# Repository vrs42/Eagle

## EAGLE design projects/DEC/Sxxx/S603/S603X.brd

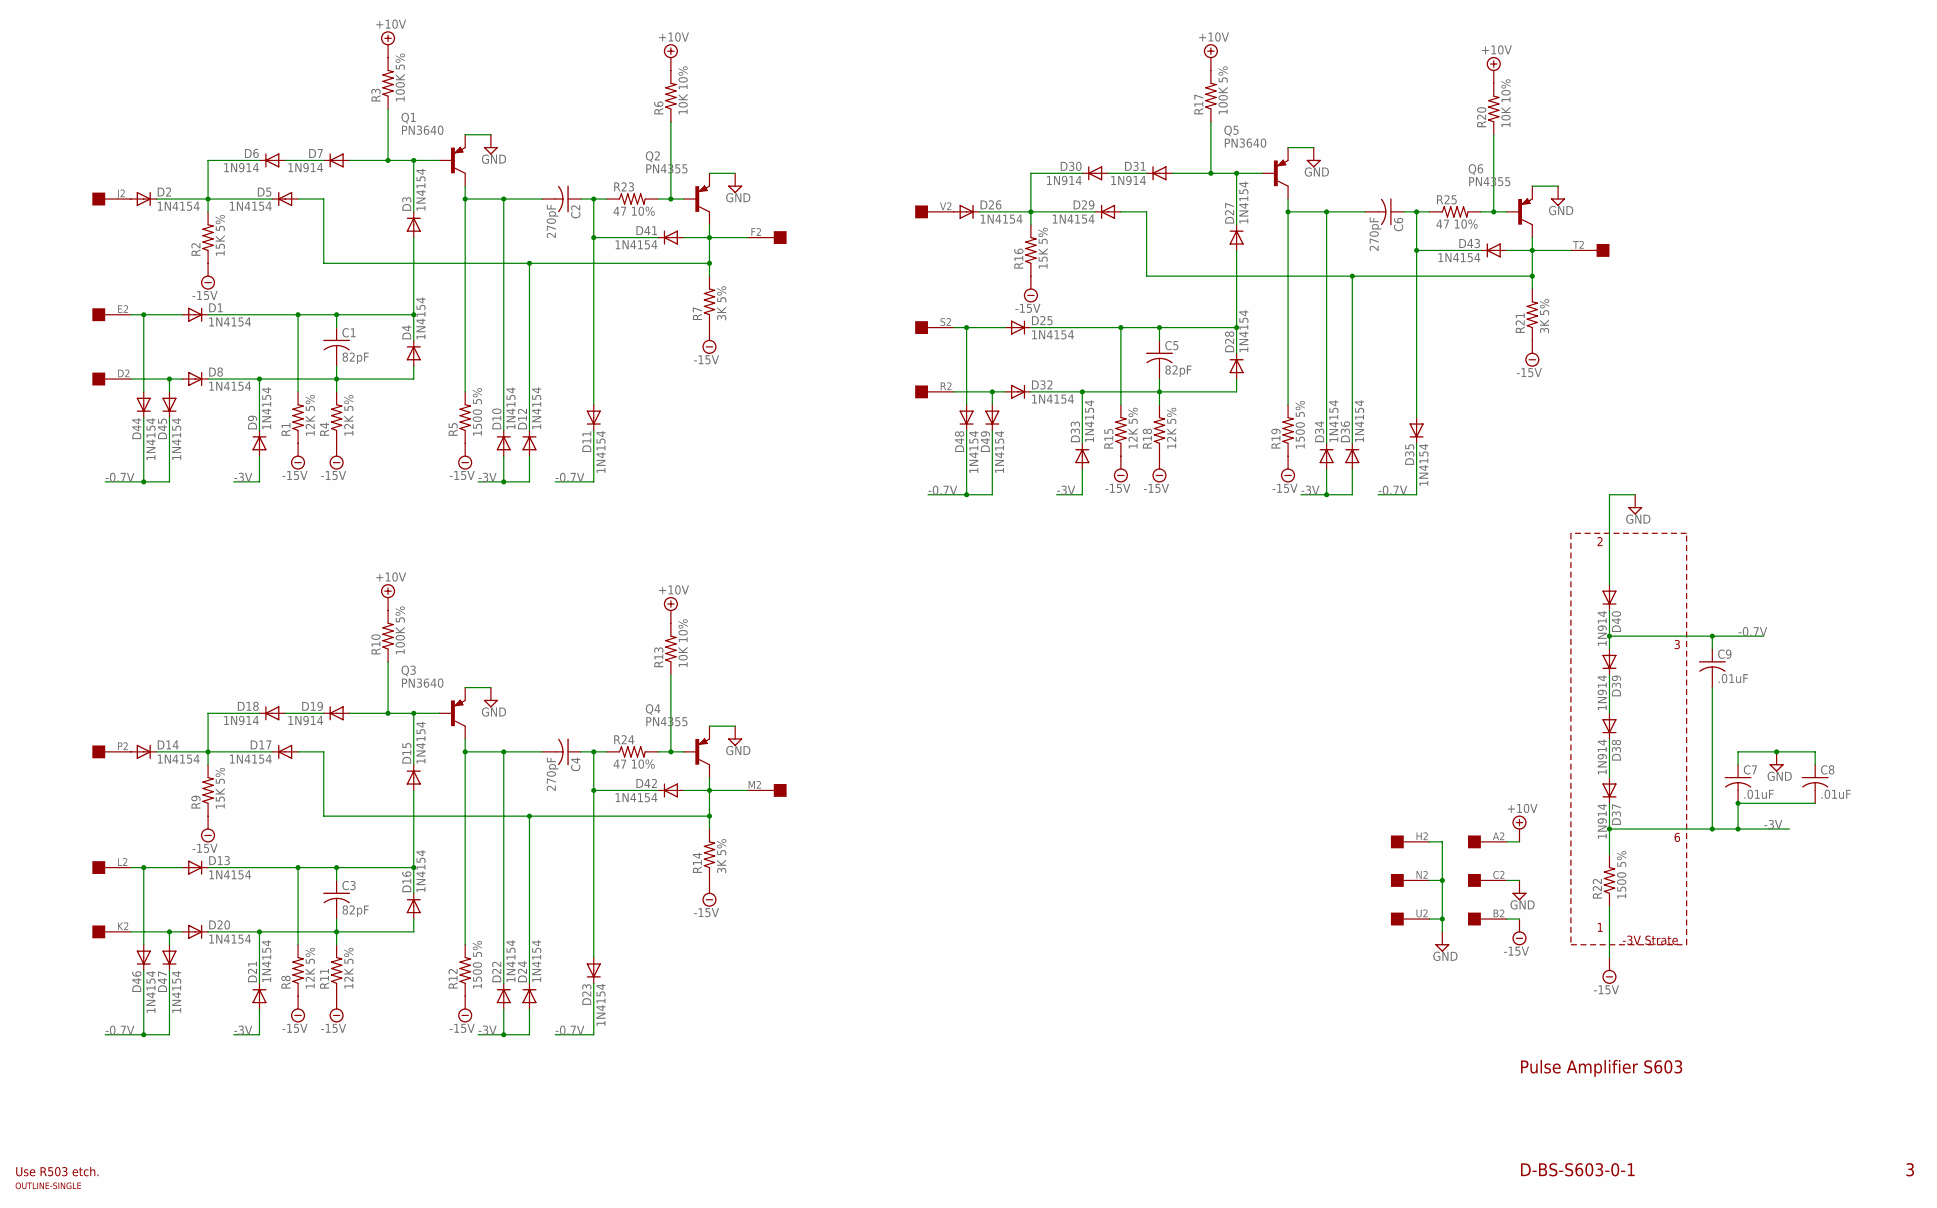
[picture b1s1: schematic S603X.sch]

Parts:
C1, C3, C5: 82pF; C050-025X075
C2, C4, C6: 270pF; C050-025X075
C7, C8, C9: .01uF; C050-025X075
D1, D2, D3, D4, D5, D8, D9, D10, D11, D12, D13, D14, D15, D16, D17, D20, D21, D22, D23, D24, D25, D26, D27, D28, D29, D32, D33, D34, D35, D36, D41, D42, D43, D44, D45, D46, D47, D48, D49: 1N4154; DO35-10
D6, D7, D18, D19, D30, D31, D37, D38, D39, D40: 1N914; DO35-10
Q1, Q3, Q5: PN3640; TO39
Q2, Q4, Q6: PN4355; TO39
R1, R4, R8, R11, R15, R18: 12K 5%; 0207/10
R2, R9, R16: 15K 5%; 0207/10
R3, R10, R17: 100K 5%; 0207/10
R5, R12, R19, R22: 1500 5%; 0207/10
R6, R13, R20: 10K 10%; 0207/10
R7, R14, R21: 3K 5%; 0207/10
R23, R24, R25: 47 10%; 0207/10
U$1: OUTLINE-SINGLE; SINGLE
U$2: EDGE-1; EDGE-CON1

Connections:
+10V: R3.2, R6.2, R10.2, R13.2, R17.2, R20.2, U$2.A2
-0.7V: C9.1, D11.C, D23.C, D35.C, D39.A, D40.C, D44.C, D45.C, D46.C, D47.C, D48.C, D49.C
-3V: C7.2, C8.2, C9.2, D9.A, D10.A, D12.A, D21.A, D22.A, D24.A, D33.A, D34.A, D36.A, D37.C, R22.2
-15V: R1.1, R2.1, R4.1, R5.1, R7.1, R8.1, R9.1, R11.1, R12.1, R14.1, R15.1, R16.1, R18.1, R19.1, R21.1, R22.1, U$2.B2
GND: C7.1, C8.1, D40.A, Q1.1 (E), Q2.1 (E), Q3.1 (E), Q4.1 (E), Q5.1 (E), Q6.1 (E), U$2.C2, U$2.H2, U$2.N2, U$2.U2
unnamed: D2.A, U$2.J2
unnamed: D2.C, D5.C, D6.C, R2.2
unnamed: D1.A, D44.A, U$2.E2
unnamed: D8.A, D45.A, U$2.D2
unnamed: C1.1, D1.C, D3.A, D4.C, R1.2
unnamed: C1.2, D4.A, D8.C, D9.C, R4.2
unnamed: D6.A, D7.C
unnamed: D38.A, D39.C
unnamed: D37.A, D38.C
unnamed: D3.C, D7.A, Q1.2 (B), R3.1
unnamed: C2.2, D10.C, Q1.3 (C), R5.2
unnamed: C2.1, D11.A, D41.C, R23.1
unnamed: Q2.2 (B), R6.1, R23.2
unnamed: D5.A, D12.C, D41.A, Q2.3 (C), R7.2, U$2.F2
unnamed: D13.A, D46.A, U$2.L2
unnamed: D20.A, D47.A, U$2.K2
unnamed: C3.1, D13.C, D15.A, D16.C, R8.2
unnamed: C3.2, D16.A, D20.C, D21.C, R11.2
unnamed: D25.A, D48.A, U$2.S2
unnamed: D32.A, D49.A, U$2.R2
unnamed: C5.1, D25.C, D27.A, D28.C, R15.2
unnamed: C5.2, D28.A, D32.C, D33.C, R18.2
unnamed: D26.A, U$2.V2
unnamed: D26.C, D29.C, D30.C, R16.2
unnamed: D30.A, D31.C
unnamed: D27.C, D31.A, Q5.2 (B), R17.1
unnamed: C6.2, D34.C, Q5.3 (C), R19.2
unnamed: C6.1, D35.A, D43.C, R25.1
unnamed: Q6.2 (B), R20.1, R25.2
unnamed: D29.A, D36.C, D43.A, Q6.3 (C), R21.2, U$2.T2
unnamed: D14.A, U$2.P2
unnamed: D14.C, D17.C, D18.C, R9.2
unnamed: D18.A, D19.C
unnamed: D15.C, D19.A, Q3.2 (B), R10.1
unnamed: C4.2, D22.C, Q3.3 (C), R12.2
unnamed: C4.1, D23.A, D42.C, R24.1
unnamed: Q4.2 (B), R13.1, R24.2
unnamed: D17.A, D24.C, D42.A, Q4.3 (C), R14.2, U$2.M2

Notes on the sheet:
Pulse Amplifier S603
D-BS-S603-0-1
-3V Strate
Use R503 etch.

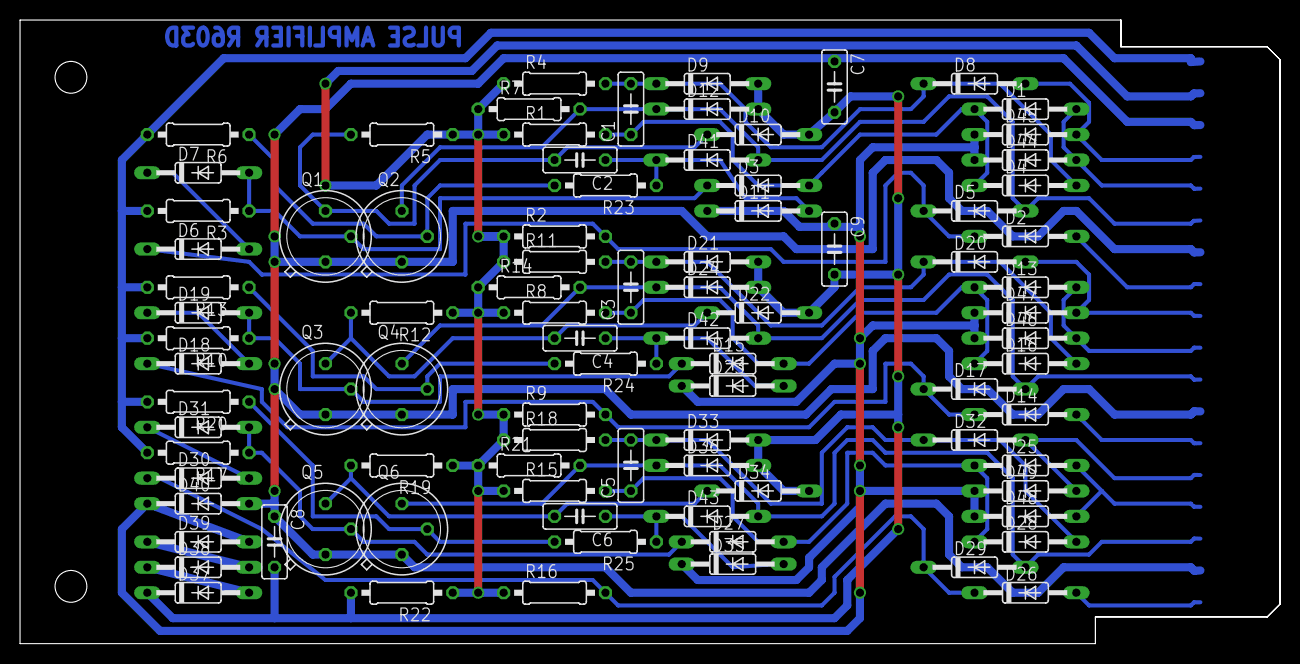
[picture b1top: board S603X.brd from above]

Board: 2 copper layers, 125.7 x 62.2 mm, 91 parts (0 on the bottom side), 43 nets.

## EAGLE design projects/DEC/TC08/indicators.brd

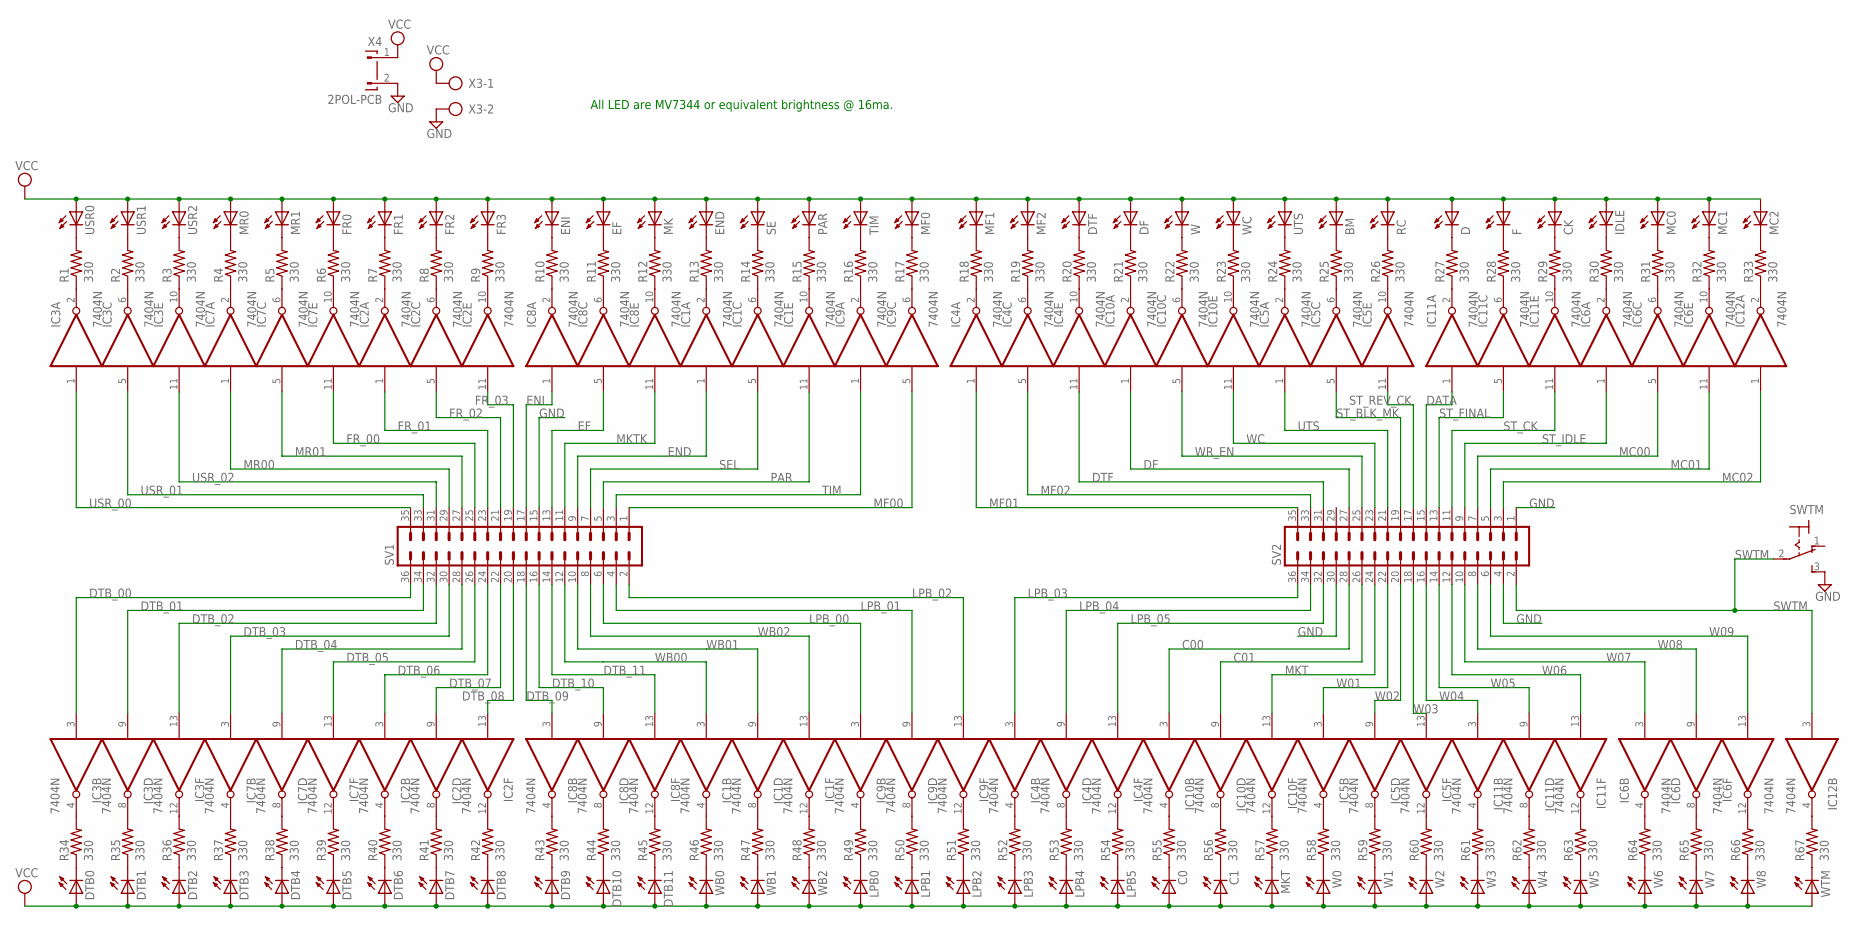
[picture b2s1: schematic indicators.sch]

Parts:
BM: LED5MM
C0, C1: LED5MM
CK: LED5MM
D: LED5MM
DF: LED5MM
DTB0, DTB1, DTB2, DTB3, DTB4, DTB5, DTB6, DTB7, DTB8, DTB9, DTB10, DTB11: LED5MM
DTF: LED5MM
EF: LED5MM
END: LED5MM
ENI: LED5MM
F: LED5MM
FR0, FR1, FR2, FR3: LED5MM
IC1, IC2, IC3, IC4, IC5, IC6, IC7, IC8, IC9, IC10, IC11, IC12: 7404N; DIL14
IDLE: LED5MM
LPB0, LPB1, LPB2, LPB3, LPB4, LPB5: LED5MM
MC0, MC1, MC2: LED5MM
MF0, MF1, MF2: LED5MM
MK: LED5MM
MKT: LED5MM
MR0, MR1: LED5MM
PAR: LED5MM
R1, R2, R3, R4, R5, R6, R7, R8, R9, R10, R11, R12, R13, R14, R15, R16, R17, R18, R19, R20, R21, R22, R23, R24, R25, R26, R27, R28, R29, R30, R31, R32, R33, R34, R35, R36, R37, R38, R39, R40, R41, R42, R43, R44, R45, R46, R47, R48, R49, R50, R51, R52, R53, R54, R55, R56, R57, R58, R59, R60, R61, R62, R63, R64, R65, R66, R67: 330; 0207/10
RC: LED5MM
SE: LED5MM
SV1, SV2: MA18-2
SWTM: M9040P
TIM: LED5MM
USR0, USR1, USR2: LED5MM
UTS: LED5MM
W, W0, W1, W2, W3, W4, W5, W6, W7, W8: LED5MM
WB0, WB1, WB2: LED5MM
WC: LED5MM
WTM: LED5MM
X3: AK300/2
X4: 2POL-PCB

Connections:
C00: IC10.3 (I), SV2.28
C01: IC10.9 (I), SV2.26
DATA: IC11.1 (I), SV2.15
DF: IC10.1 (I), SV2.27
DTB_00: IC3.3 (I), SV1.36
DTB_01: IC3.9 (I), SV1.34
DTB_02: IC3.13 (I), SV1.32
DTB_03: IC7.3 (I), SV1.30
DTB_04: IC7.9 (I), SV1.28
DTB_05: IC7.13 (I), SV1.26
DTB_06: IC2.3 (I), SV1.24
DTB_07: IC2.9 (I), SV1.22
DTB_08: IC2.13 (I), SV1.20
DTB_09: IC8.3 (I), SV1.18
DTB_10: IC8.9 (I), SV1.16
DTB_11: IC8.13 (I), SV1.14
DTF: IC4.11 (I), SV2.31
EF: IC8.5 (I), SV1.13
END: IC1.1 (I), SV1.9
ENI: IC8.1 (I), SV1.17
FR_00: IC7.11 (I), SV1.25
FR_01: IC2.1 (I), SV1.23
FR_02: IC2.5 (I), SV1.21
FR_03: IC2.11 (I), SV1.19
GND: IC1.7 (GND), IC2.7 (GND), IC3.7 (GND), IC4.7 (GND), IC5.7 (GND), IC6.7 (GND), IC7.7 (GND), IC8.7 (GND), IC9.7 (GND), IC10.7 (GND), IC11.7 (GND), IC12.7 (GND), SV1.15, SV2.1, SV2.4, SV2.30, SWTM.3 (S), X3.2, X4.2
LPB_00: IC9.3 (I), SV1.6
LPB_01: IC9.9 (I), SV1.4
LPB_02: IC9.13 (I), SV1.2
LPB_03: IC4.3 (I), SV2.36
LPB_04: IC4.9 (I), SV2.34
LPB_05: IC4.13 (I), SV2.32
MC00: IC6.5 (I), SV2.7
MC01: IC6.11 (I), SV2.5
MC02: IC12.1 (I), SV2.3
MF00: IC9.5 (I), SV1.1
MF01: IC4.1 (I), SV2.35
MF02: IC4.5 (I), SV2.33
MKT: IC10.13 (I), SV2.24
MKTK: IC8.11 (I), SV1.11
MR00: IC7.1 (I), SV1.29
MR01: IC7.5 (I), SV1.27
unnamed: R1.2, USR0.K (C)
unnamed: R2.2, USR1.K (C)
unnamed: R3.2, USR2.K (C)
unnamed: MR0.K (C), R4.2
unnamed: MR1.K (C), R5.2
unnamed: FR0.K (C), R6.2
unnamed: FR1.K (C), R7.2
unnamed: FR2.K (C), R8.2
unnamed: FR3.K (C), R9.2
unnamed: ENI.K (C), R10.2
unnamed: EF.K (C), R11.2
unnamed: MK.K (C), R12.2
unnamed: END.K (C), R13.2
unnamed: R14.2, SE.K (C)
unnamed: PAR.K (C), R15.2
unnamed: R16.2, TIM.K (C)
unnamed: MF0.K (C), R17.2
unnamed: MF1.K (C), R18.2
unnamed: MF2.K (C), R19.2
unnamed: IC3.2 (O), R1.1
unnamed: IC3.6 (O), R2.1
unnamed: IC3.10 (O), R3.1
unnamed: IC7.2 (O), R4.1
unnamed: IC7.6 (O), R5.1
unnamed: IC7.10 (O), R6.1
unnamed: IC2.2 (O), R7.1
unnamed: IC2.6 (O), R8.1
unnamed: IC2.10 (O), R9.1
unnamed: IC8.2 (O), R10.1
unnamed: IC8.6 (O), R11.1
unnamed: IC8.10 (O), R12.1
unnamed: IC1.2 (O), R13.1
unnamed: IC1.6 (O), R14.1
unnamed: IC1.10 (O), R15.1
unnamed: IC9.2 (O), R16.1
unnamed: IC9.6 (O), R17.1
unnamed: IC4.2 (O), R18.1
unnamed: DTF.K (C), R20.2
unnamed: DF.K (C), R21.2
unnamed: R22.2, W.K (C)
unnamed: R23.2, WC.K (C)
unnamed: R24.2, UTS.K (C)
unnamed: BM.K (C), R25.2
unnamed: R26.2, RC.K (C)
unnamed: D.K (C), R27.2
unnamed: F.K (C), R28.2
unnamed: CK.K (C), R29.2
unnamed: IDLE.K (C), R30.2
unnamed: MC0.K (C), R31.2
unnamed: MC1.K (C), R32.2
unnamed: MC2.K (C), R33.2
unnamed: IC4.6 (O), R19.1
unnamed: IC4.10 (O), R20.1
unnamed: IC10.2 (O), R21.1
unnamed: IC10.10 (O), R23.1
unnamed: IC10.6 (O), R22.1
unnamed: IC5.2 (O), R24.1
unnamed: IC5.6 (O), R25.1
unnamed: IC5.10 (O), R26.1
unnamed: IC11.2 (O), R27.1
unnamed: IC11.6 (O), R28.1
unnamed: IC11.10 (O), R29.1
unnamed: IC6.2 (O), R30.1
unnamed: IC6.6 (O), R31.1
unnamed: IC6.10 (O), R32.1
unnamed: IC12.2 (O), R33.1
unnamed: DTB0.K (C), R34.1
unnamed: DTB1.K (C), R35.1
unnamed: DTB2.K (C), R36.1
unnamed: DTB3.K (C), R37.1
unnamed: DTB4.K (C), R38.1
unnamed: DTB5.K (C), R39.1
unnamed: DTB6.K (C), R40.1
unnamed: DTB7.K (C), R41.1
unnamed: DTB8.K (C), R42.1
unnamed: DTB9.K (C), R43.1
unnamed: DTB10.K (C), R44.1
unnamed: DTB11.K (C), R45.1
unnamed: R46.1, WB0.K (C)
unnamed: R47.1, WB1.K (C)
unnamed: R48.1, WB2.K (C)
unnamed: LPB0.K (C), R49.1
unnamed: LPB1.K (C), R50.1
unnamed: LPB2.K (C), R51.1
unnamed: LPB3.K (C), R52.1
unnamed: LPB4.K (C), R53.1
unnamed: LPB5.K (C), R54.1
unnamed: C0.K (C), R55.1
unnamed: C1.K (C), R56.1
unnamed: MKT.K (C), R57.1
unnamed: R58.1, W0.K (C)
unnamed: R59.1, W1.K (C)
unnamed: R60.1, W2.K (C)
unnamed: R61.1, W3.K (C)
unnamed: R62.1, W4.K (C)
unnamed: R63.1, W5.K (C)
unnamed: R64.1, W6.K (C)
unnamed: R65.1, W7.K (C)
unnamed: R66.1, W8.K (C)
unnamed: R67.1, WTM.K (C)
unnamed: IC3.4 (O), R34.2
unnamed: IC3.8 (O), R35.2
unnamed: IC3.12 (O), R36.2
unnamed: IC7.4 (O), R37.2
unnamed: IC7.8 (O), R38.2
unnamed: IC7.12 (O), R39.2
unnamed: IC2.4 (O), R40.2
unnamed: IC2.8 (O), R41.2
unnamed: IC2.12 (O), R42.2
unnamed: IC8.4 (O), R43.2
unnamed: IC8.8 (O), R44.2
unnamed: IC8.12 (O), R45.2
unnamed: IC1.4 (O), R46.2
unnamed: IC1.8 (O), R47.2
unnamed: IC1.12 (O), R48.2
unnamed: IC9.4 (O), R49.2
unnamed: IC9.8 (O), R50.2
unnamed: IC9.12 (O), R51.2
unnamed: IC4.4 (O), R52.2
unnamed: IC4.8 (O), R53.2
unnamed: IC4.12 (O), R54.2
unnamed: IC10.4 (O), R55.2
unnamed: IC10.8 (O), R56.2
unnamed: IC10.12 (O), R57.2
unnamed: IC5.4 (O), R58.2
unnamed: IC5.8 (O), R59.2
unnamed: IC5.12 (O), R60.2
unnamed: IC11.4 (O), R61.2
unnamed: IC11.8 (O), R62.2
unnamed: IC11.12 (O), R63.2
unnamed: IC6.4 (O), R64.2
unnamed: IC6.8 (O), R65.2
unnamed: IC6.12 (O), R66.2
unnamed: IC12.4 (O), R67.2
PAR: IC1.11 (I), SV1.5
SEL: IC1.5 (I), SV1.7
ST_BLK_MK: IC5.5 (I), SV2.19
ST_CK: IC11.11 (I), SV2.11
ST_FINAL: IC11.5 (I), SV2.13
ST_IDLE: IC6.1 (I), SV2.9
ST_REV_CK: IC5.11 (I), SV2.17
SWTM: IC12.3 (I), SV2.2, SWTM.2
TIM: IC9.1 (I), SV1.3
USR_00: IC3.1 (I), SV1.35
USR_01: IC3.5 (I), SV1.33
USR_02: IC3.11 (I), SV1.31
UTS: IC5.1 (I), SV2.21
VCC: BM.A, C0.A, C1.A, CK.A, D.A, DF.A, DTB0.A, DTB1.A, DTB2.A, DTB3.A, DTB4.A, DTB5.A, DTB6.A, DTB7.A, DTB8.A, DTB9.A, DTB10.A, DTB11.A, DTF.A, EF.A, END.A, ENI.A, F.A, FR0.A, FR1.A, FR2.A, FR3.A, IC1.14 (VCC), IC2.14 (VCC), IC3.14 (VCC), IC4.14 (VCC), IC5.14 (VCC), IC6.14 (VCC), IC7.14 (VCC), IC8.14 (VCC), IC9.14 (VCC), IC10.14 (VCC), IC11.14 (VCC), IC12.14 (VCC), IDLE.A, LPB0.A, LPB1.A, LPB2.A, LPB3.A, LPB4.A, LPB5.A, MC0.A, MC1.A, MC2.A, MF0.A, MF1.A, MF2.A, MK.A, MKT.A, MR0.A, MR1.A, PAR.A, RC.A, SE.A, TIM.A, USR0.A, USR1.A, USR2.A, UTS.A, W.A, W0.A, W1.A, W2.A, W3.A, W4.A, W5.A, W6.A, W7.A, W8.A, WB0.A, WB1.A, WB2.A, WC.A, WTM.A, X3.1, X4.1
W01: IC5.3 (I), SV2.22
W02: IC5.9 (I), SV2.20
W03: IC5.13 (I), SV2.18
W04: IC11.3 (I), SV2.16
W05: IC11.9 (I), SV2.14
W06: IC11.13 (I), SV2.12
W07: IC6.3 (I), SV2.10
W08: IC6.9 (I), SV2.8
W09: IC6.13 (I), SV2.6
WB00: IC1.3 (I), SV1.12
WB01: IC1.9 (I), SV1.10
WB02: IC1.13 (I), SV1.8
WC: IC10.11 (I), SV2.23
WR_EN: IC10.5 (I), SV2.25

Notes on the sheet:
All LED are MV7344 or equivalent brightness @ 16ma.

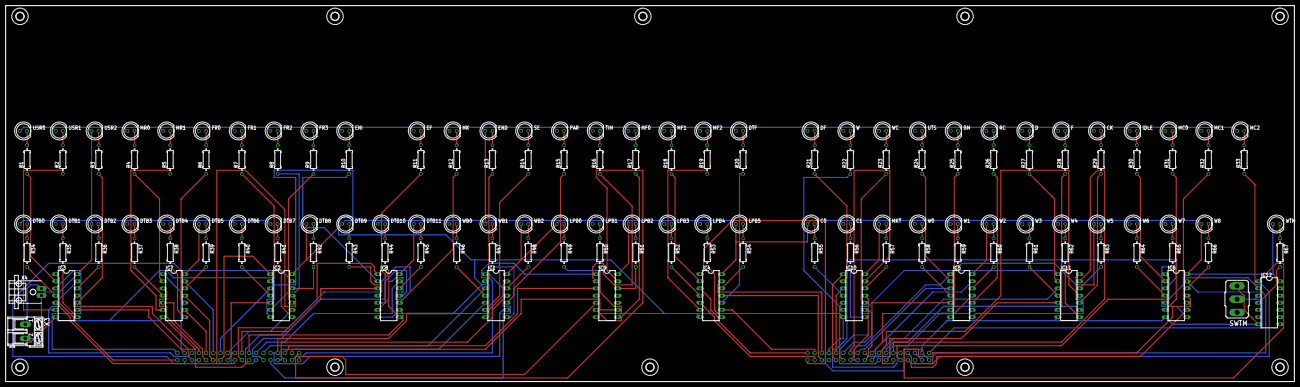
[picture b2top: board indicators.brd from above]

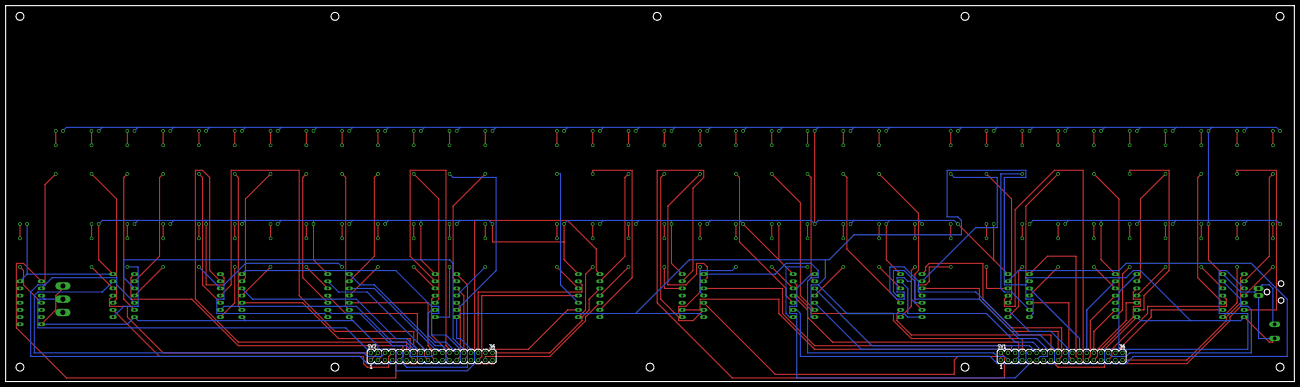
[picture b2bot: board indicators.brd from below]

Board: 2 copper layers, 457.2 x 133.4 mm, 161 parts (2 on the bottom side), 203 nets.

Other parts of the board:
U$1, U$2, U$3, U$4, U$5, U$6, U$7, U$8, U$9, U$10: 2,8

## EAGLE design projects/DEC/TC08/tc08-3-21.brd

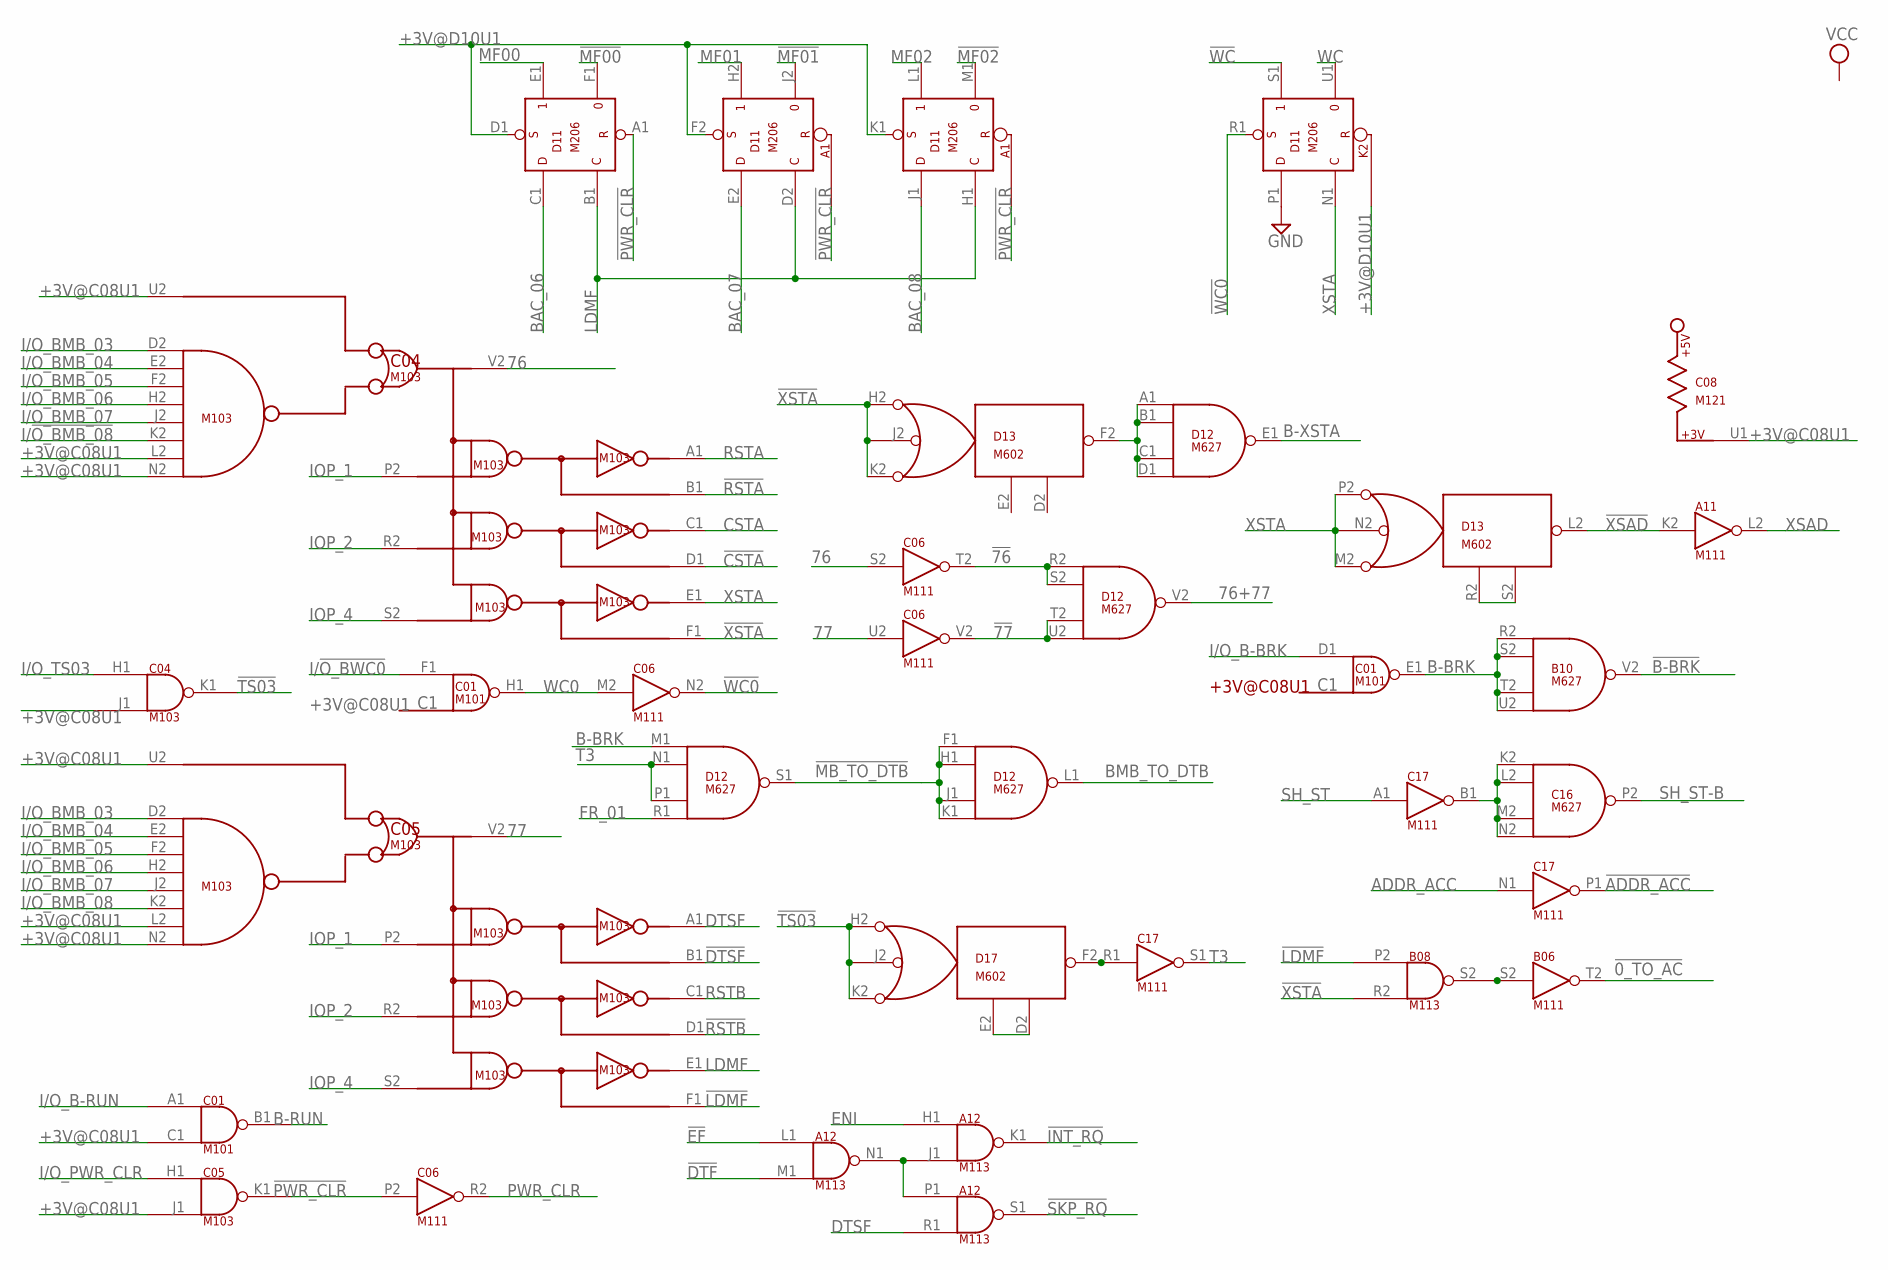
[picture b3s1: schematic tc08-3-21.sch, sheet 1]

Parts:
A11: M111; H807
A12: M113; H807
B06: M111; H807
B08: M113; H807
B10: M627; H807
C01: M101; H807
C04, C05: M103; H807
C06, C17: M111; H807
C08: M121; H807
C16: M627; H807
D11: M206; H807
D12: M627; H807
D13, D17: M602; H807

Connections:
76: C04.V2, C06.S2 (IN)
76+77: D12.V2 (OUT); also elsewhere on the board
77: C05.V2, C06.U2 (IN)
!0_TO_AC: B06.T2 (OUT); also elsewhere on the board
!76: C06.T2 (OUT), D12.R2 (IN1), D12.S2 (IN2)
!77: C06.V2 (OUT), D12.T2 (IN3), D12.U2 (IN4)
!ADDR_ACC: C17.P1 (OUT); also elsewhere on the board
!B-BRK: B10.V2 (OUT); also elsewhere on the board
!CSTA: C04.D1; also elsewhere on the board
!DTF: A12.M1 (IN2); also elsewhere on the board
!DTSF: C05.B1
!EF: A12.L1 (IN1); also elsewhere on the board
!INT_RQ: A12.K1 (OUT); also elsewhere on the board
!LDMF: B08.P2 (IN1), C05.F1
!MB_TO_DTB: D12.F1 (IN1), D12.H1 (IN2), D12.J1 (IN3), D12.K1 (IN4), D12.S1 (OUT)
!MF00: D11.F1 (0); also elsewhere on the board
!MF01: D11.J2 (0); also elsewhere on the board
!MF02: D11.M1 (0); also elsewhere on the board
!PWR_CLR: C05.K1 (OUT), C06.P2 (IN), D11.A1 (R); also elsewhere on the board
!RSTA: C04.B1; also elsewhere on the board
!RSTB: C05.D1; also elsewhere on the board
!SKP_RQ: A12.S1 (OUT); also elsewhere on the board
!TS03: C04.K1 (OUT), D17.H2, D17.J2, D17.K2
!WC: D11.S1 (1); also elsewhere on the board
!WC0: C06.N2 (OUT), D11.R1 (S)
!XSAD: A11.K2 (IN), D13.L2 (F2)
!XSTA: B08.R2 (IN2), C04.F1, D13.H2, D13.J2, D13.K2; also elsewhere on the board
+3V@C08U1: C01.C1 (IN2), C04.J1 (IN2), C04.L2, C04.N2, C04.U2, C05.J1 (IN2), C05.L2, C05.N2, C05.U2, C08.U1; also elsewhere on the board
+3V@D10U1: D11.D1 (S), D11.F2 (S), D11.K1 (S); also elsewhere on the board
ADDR_ACC: C17.N1 (IN); also elsewhere on the board
B-BRK: B10.R2 (IN1), B10.S2 (IN2), B10.T2 (IN3), B10.U2 (IN4), C01.E1 (OUT), D12.M1 (IN1)
B-RUN: C01.B1 (OUT); also elsewhere on the board
B-XSTA: D12.E1 (OUT); also elsewhere on the board
BAC_06: D11.C1 (D); also elsewhere on the board
BAC_07: D11.E2 (D); also elsewhere on the board
BAC_08: D11.J1 (D); also elsewhere on the board
BMB_TO_DTB: D12.L1 (OUT); also elsewhere on the board
CSTA: C04.C1; also elsewhere on the board
DTSF: A12.R1 (IN2), C05.A1
ENI: A12.H1 (IN1); also elsewhere on the board
FR_01: D12.R1 (IN4); also elsewhere on the board
GND: A11.C2 (GND), A11.T1 (GND), A12.C2 (GND), A12.T1 (GND), B06.C2 (GND), B06.T1 (GND), B08.C2 (GND), B08.T1 (GND), B10.C2 (GND), B10.T1 (GND), C01.C2 (GND), C01.T1 (GND), C04.C2 (GND), C04.T1 (GND), C05.C2 (GND), C05.T1 (GND), C06.C2 (GND), C06.T1 (GND), C08.C2 (GND), C08.T1 (GND), C16.C2 (GND), C16.T1 (GND), C17.C2 (GND), C17.T1 (GND), D11.C2 (GND), D11.P1 (D), D11.T1 (GND), D12.C2 (GND), D12.T1 (GND), D13.C2 (GND), D17.C2 (GND); also elsewhere on the board
I/!O_BMB_08: C04.K2; also elsewhere on the board
I/!O_BWC0: C01.F1 (IN); also elsewhere on the board
I/O_B-BRK: C01.D1 (IN); also elsewhere on the board
I/O_B-RUN: C01.A1 (IN1); also elsewhere on the board
I/O_BMB_03: C04.D2, C05.D2; also elsewhere on the board
I/O_BMB_04: C04.E2, C05.E2; also elsewhere on the board
I/O_BMB_05: C04.F2, C05.F2; also elsewhere on the board
I/O_BMB_06: C04.H2, C05.H2; also elsewhere on the board
I/O_BMB_07: C04.J2, C05.J2; also elsewhere on the board
I/O_BMB_08: C05.K2; also elsewhere on the board
I/O_PWR_CLR: C05.H1 (IN1); also elsewhere on the board
I/O_TS03: C04.H1 (IN1); also elsewhere on the board
IOP_1: C04.P2, C05.P2; also elsewhere on the board
IOP_2: C04.R2, C05.R2; also elsewhere on the board
IOP_4: C04.S2, C05.S2; also elsewhere on the board
LDMF: C05.E1, D11.B1 (C), D11.D2 (C), D11.H1 (C)
MF00: D11.E1 (1); also elsewhere on the board
MF01: D11.H2 (1); also elsewhere on the board
MF02: D11.L1 (1); also elsewhere on the board
unnamed: B06.S2 (IN), B08.S2 (OUT)
unnamed: C16.K2 (IN1), C16.L2 (IN2), C16.M2 (IN3), C16.N2 (IN4), C17.B1 (OUT)
unnamed: D13.R2 (E2), D13.S2 (D2)
unnamed: D12.A1 (IN1), D12.B1 (IN2), D12.C1 (IN3), D12.D1 (IN4), D13.F2
unnamed: A12.J1 (IN2), A12.N1 (OUT), A12.P1 (IN1)
unnamed: C17.R1 (IN), D17.F2
unnamed: D17.D2, D17.E2
PWR_CLR: C06.R2 (OUT)
RSTA: C04.A1
RSTB: C05.C1
SH_ST: C17.A1 (IN); also elsewhere on the board
SH_ST-B: C16.P2 (OUT); also elsewhere on the board
T3: C17.S1 (OUT), D12.N1 (IN2), D12.P1 (IN3)
VCC: A11.A2 (VCC), A12.A2 (VCC), B06.A2 (VCC), B08.A2 (VCC), B10.A2 (VCC), C01.A2 (VCC), C04.A2 (VCC), C05.A2 (VCC), C06.A2 (VCC), C08.A2 (VCC), C16.A2 (VCC), C17.A2 (VCC), D11.A2 (VCC), D12.A2 (VCC), D13.A2 (VCC), D17.A2 (VCC); also elsewhere on the board
WC: D11.U1 (0); also elsewhere on the board
WC0: C01.H1 (OUT), C06.M2 (IN)
XSAD: A11.L2 (OUT); also elsewhere on the board
XSTA: C04.E1, D11.N1 (C), D13.M2 (K2), D13.N2 (J2), D13.P2 (H2); also elsewhere on the board

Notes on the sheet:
+3V@C08U1
